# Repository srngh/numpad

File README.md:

KiCAD Project files for a nice!nano powered numpad.

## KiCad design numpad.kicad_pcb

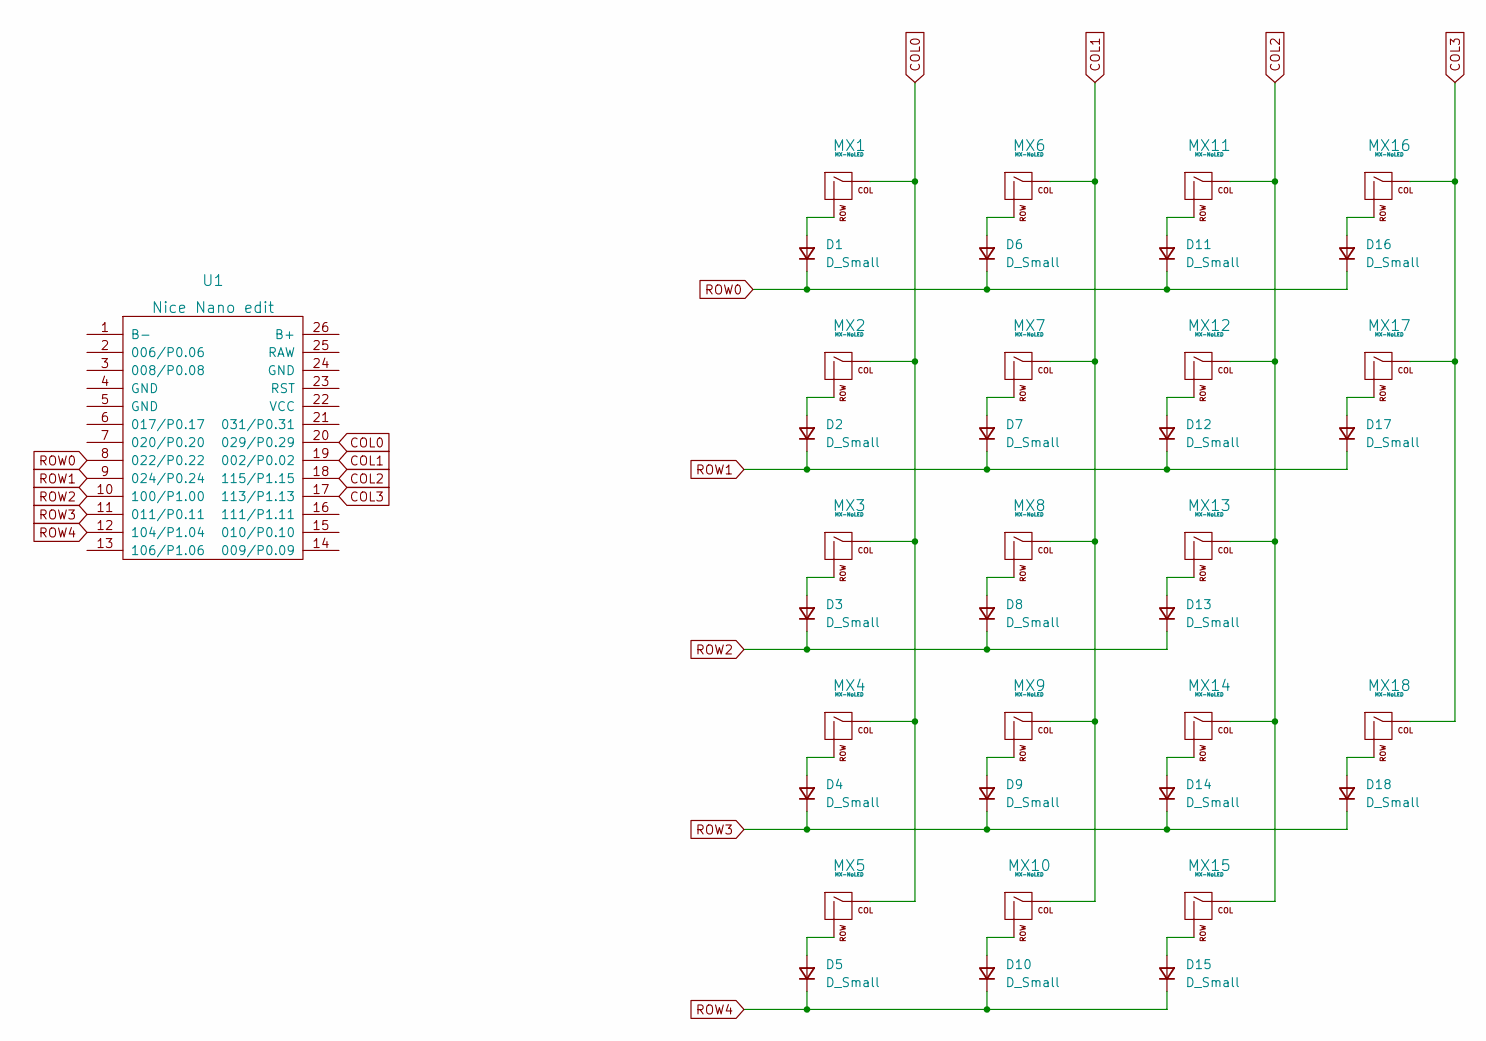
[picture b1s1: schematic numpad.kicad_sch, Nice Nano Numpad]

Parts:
D1, D2, D3, D4, D5, D6, D7, D8, D9, D10, D11, D12, D13, D14, D15, D16, D17, D18: D_Small; D_SOD-123
MX1, MX2, MX3, MX4, MX5, MX6, MX7, MX8, MX9, MX10, MX11, MX12, MX13, MX14, MX15, MX16: MX-NoLED; MXOnly-1U-Hotswap
MX17, MX18: MX-NoLED; MXOnly-2U-Hotswap-VerticalStabilizers
U1: Nice Nano edit; ArduinoProMicro-ZigZag-DoubleSided

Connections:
COL0: MX1.1 (COL), MX2.1 (COL), MX3.1 (COL), MX4.1 (COL), MX5.1 (COL), U1.20 (029/P0.29)
COL1: MX6.1 (COL), MX7.1 (COL), MX8.1 (COL), MX9.1 (COL), MX10.1 (COL), U1.19 (002/P0.02)
COL2: MX11.1 (COL), MX12.1 (COL), MX13.1 (COL), MX14.1 (COL), MX15.1 (COL), U1.18 (115/P1.15)
COL3: MX16.1 (COL), MX17.1 (COL), MX18.1 (COL), U1.17 (113/P1.13)
unnamed: D1.2 (A), MX1.2 (ROW)
unnamed: D2.2 (A), MX2.2 (ROW)
unnamed: D3.2 (A), MX3.2 (ROW)
unnamed: D4.2 (A), MX4.2 (ROW)
unnamed: D5.2 (A), MX5.2 (ROW)
unnamed: D6.2 (A), MX6.2 (ROW)
unnamed: D7.2 (A), MX7.2 (ROW)
unnamed: D8.2 (A), MX8.2 (ROW)
unnamed: D9.2 (A), MX9.2 (ROW)
unnamed: D10.2 (A), MX10.2 (ROW)
unnamed: D11.2 (A), MX11.2 (ROW)
unnamed: D12.2 (A), MX12.2 (ROW)
unnamed: D13.2 (A), MX13.2 (ROW)
unnamed: D14.2 (A), MX14.2 (ROW)
unnamed: D15.2 (A), MX15.2 (ROW)
unnamed: D16.2 (A), MX16.2 (ROW)
unnamed: D17.2 (A), MX17.2 (ROW)
unnamed: D18.2 (A), MX18.2 (ROW)
ROW0: D1.1 (K), D6.1 (K), D11.1 (K), D16.1 (K), U1.8 (022/P0.22)
ROW1: D2.1 (K), D7.1 (K), D12.1 (K), D17.1 (K), U1.9 (024/P0.24)
ROW2: D3.1 (K), D8.1 (K), D13.1 (K), U1.10 (100/P1.00)
ROW3: D4.1 (K), D9.1 (K), D14.1 (K), D18.1 (K), U1.11 (011/P0.11)
ROW4: D5.1 (K), D10.1 (K), D15.1 (K), U1.12 (104/P1.04)

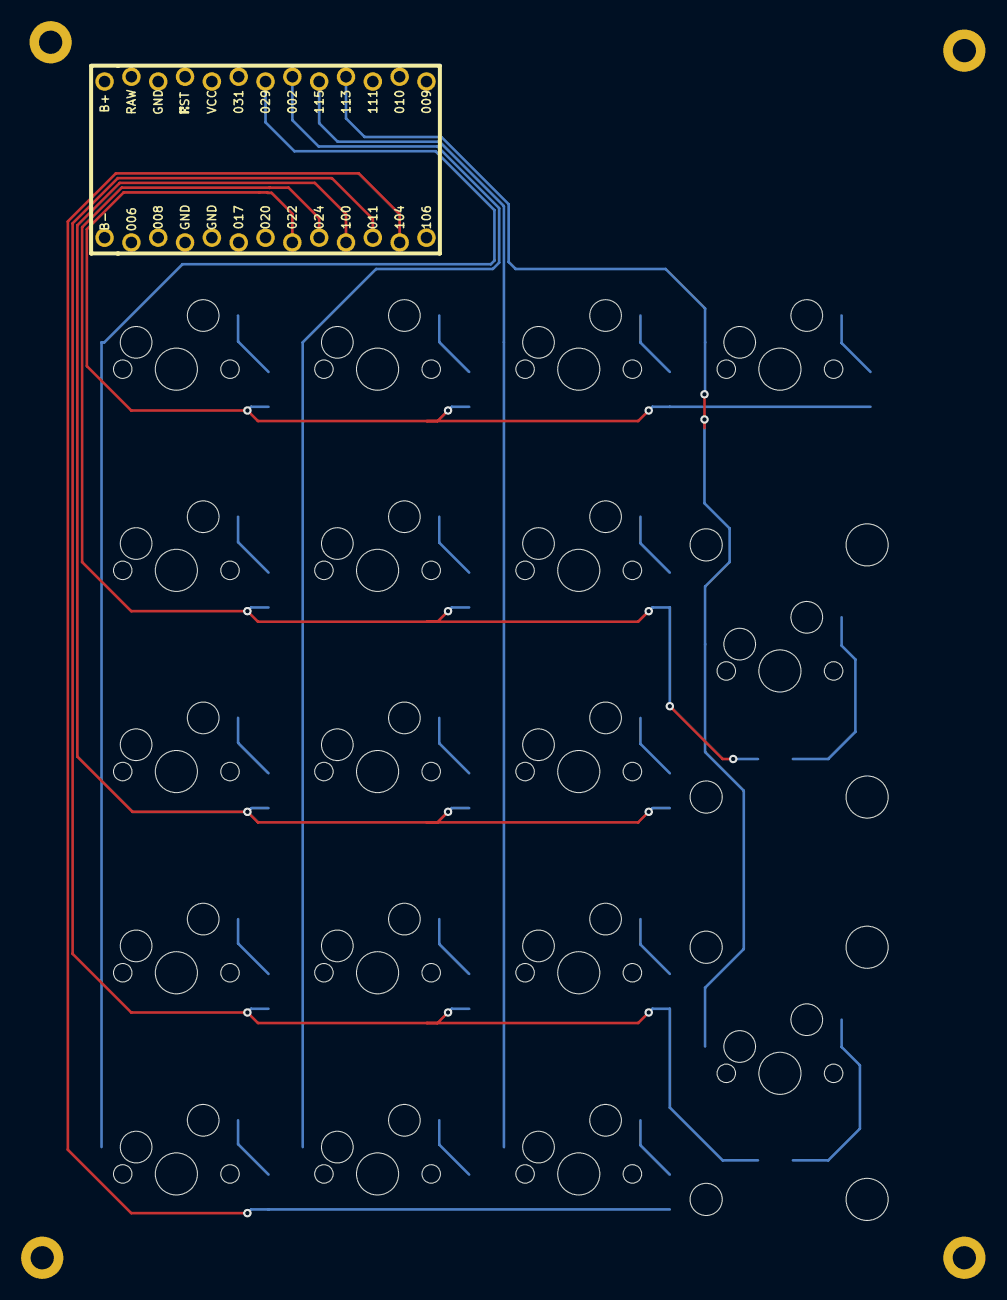
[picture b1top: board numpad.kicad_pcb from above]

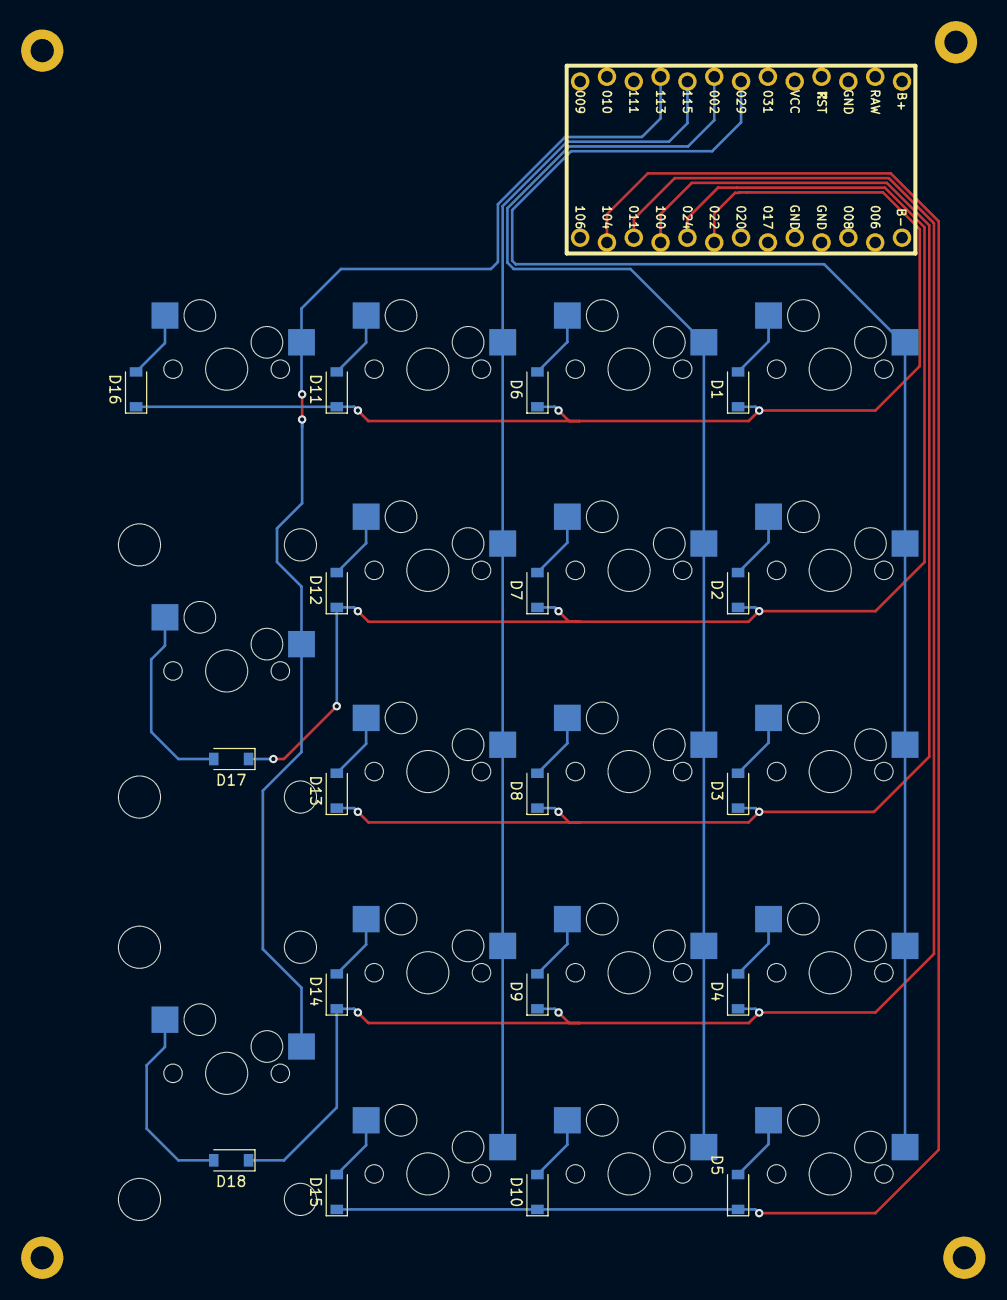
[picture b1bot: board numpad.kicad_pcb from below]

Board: 2 copper layers, 38 parts (18 on the bottom side), 27 nets.

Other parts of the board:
TH1: HOLE; M2_HOLE_PCB

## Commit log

2023-04-11 add submodules
2023-05-08 add README
